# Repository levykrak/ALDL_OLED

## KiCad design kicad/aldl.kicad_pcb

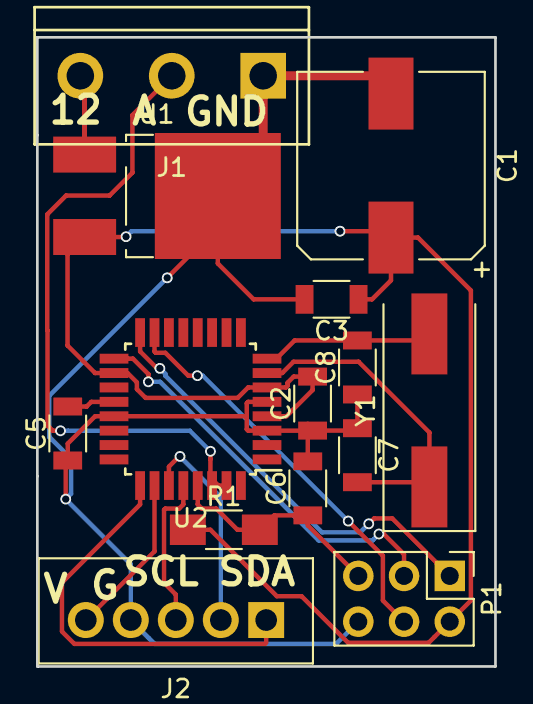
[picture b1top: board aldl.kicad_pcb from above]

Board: 2 copper layers, 25.5 x 35.0 mm, 14 parts (0 on the bottom side), 15 nets.

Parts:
C1: 470uF; CP_Elec_10x10
C2, C3, C5, C6: 100nF; C_1206
C7, C8: 27pF; C_1206
J1: CONN_01X03; bornier3
J2: wyswietlacz; Wafer_Vertical15x5.8x7RM2.5-5
P1: CONN_3X2; Pin_Header_Straight_2x03_Pitch2.54mm
R1: 10k; R_1206_HandSoldering
U1: LM7805; TO-252-2_Rectifier
U2: ATMEGA328P-AU; TQFP-32_7x7mm_Pitch0.8mm
Y1: 16MHz; Crystal_SMD_HC49-SD

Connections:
+5V: C1.1, C2.2, C3.1, P1.2, R1.1, U1.3, U2.4, U2.6, U2.18
+12V: J1.3, U1.1
/ALDL: J1.2, U2.30, U2.31
/OLED2_PWR: J2.1, U2.25
/OLED_PWR: J2.5, U2.26
/SCL: J2.3, U2.28
/SDA: J2.2, U2.27
GND: C1.2, C2.1, C3.2, C5.1, C6.2, C7.1, C8.1, J1.1, J2.4, P1.6, U1.2, U2.3, U2.5, U2.21
MISO: P1.1, U2.16
MOSI: P1.4, U2.15
unnamed: C5.2, U2.20
unnamed: C7.2, U2.7, Y1.1
unnamed: C8.2, U2.8, Y1.2
RST: C6.1, P1.5, R1.2, U2.29
SCK: P1.3, U2.17

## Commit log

2019-04-29 first commit. working aldl_dziala
2019-04-29 test pliku
2019-04-29 wywalony wpis w pliku
